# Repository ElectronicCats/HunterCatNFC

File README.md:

# Hunter Cat NFC

<p align=center>

<p align=center>

</p>

## How does the Hunter Cat NFC work?

The Hunter Cat NFC is a security tool for contactless (Near Field Communication) used in access control, identification, and bank cards. It is specially created to identify NFC readers and sniffing tools. With this tool, you can audit, read or emulate cards of different types.

## Understanding the Hunter Cat NFC and its LEDs 

The device has preloaded reader detection firmware that lets the user know when is near an NFC reader attempting to read his card.

### Reader detection 

To detect hidden readers seeking to read your cards without authorization for cloning.

1. Turn on Hunter Cat NFC
2. Wait for the LEDs to turn off
3. Red LED flashes every 1 second
4. Approach the reader, the Hunter Cat NFC LEDs should light up indicating if an NFC reader was detected
5. If it does not turn on and the LED stays on, it is not near an NFC reader

## How does it work? 

Hunter Cat NFC can be set to behave either as an NFC reader, a tag, or to establish a two-way connection with another NFC device.

NFC USB Dongle features a SAMD21 MCU which works in conjunction with the PN7150. The USB interface is provided by SAMD21 MCU, and the NFC functionality is ensured thanks to PN7150.

NFC is designed to be intuitive for users. The communication between two devices is established in the simplest way possible — by bringing them close to each other. NFC frontend can operate in three distinct modes:

### Card emulation mode — where Hunter Cat NFC behaves like a smart card or a tag

In this mode, Hunter Cat NFC emulates a NFC tag. It doesn’t initiate the communication, it only responds to a NFC reader. A typical application of the card emulation mode is how people use NFC in their smartphones to replace several cards, badges or tags at once (using the same phone for RFID access controls, contactless payments and so on). Card emulation mode, however, is not limited to smartphones but can be used for any portable device.

### Read/Write — where Hunter Cat NFC behaves as an NFC Reader/Writer

Here, Hunter Cat NFC communicates with a passive tag, NFC smart card, or an NFC device operating in card emulation mode. It can read or write to a tag (although reading is a more common use-case because tags will often be write protected). In this mode, the Hunter Cat NFC generates the RF field, while a tag or card only modulates it.

### Peer-to-peer — for more complex interactions

Peer-to-peer mode establishes a two-way communication channel between a pair of NFC-enabled devices. When a user brings two devices close to each other, the two NFC chips establish a P2P connection and exchange data.

## Characteristics:
* Procesador Cortex M0+
* USB C 2.0
* NFC Reader, Card and NFC Forum
* Arduino compatible
* CircuitPython compatible
* UF2 Bootloader
* 3 LEDs status
* Open Hardware
* Battery
* RF protocols supported
  * NFCIP-1, NFCIP-2 protocol 
  * ISO/IEC 14443A, ISO/IEC 14443B PICC, NFC Forum T4T modes via host interface
  * NFC Forum T3T via host interface
  * ISO/IEC 14443A, ISO/IEC 14443B PCD designed according to NFC Forum digital protocol T4T platform and ISO-DEP 
  * FeliCa PCD mode
  * MIFARE Classic PCD encryption mechanism (MIFARE Classic 1K/4K)
  * NFC Forum tag 1 to 5 (MIFARE Ultralight, Jewel, Open FeliCa tag, MIFAREDESFire
  * ISO/IEC 15693/ICODE VCD mode 
  * Includes NXP ISO/IEC14443-A and Innovatron ISO/IEC14443-B intellectual property licensing rights

## Disclaimer
>[!IMPORTANT]
>Hunter Cat NFC, is a wireless penetration testing tool intended solely for use in authorized security audits, where such usage is permitted by applicable laws and regulations. Before utilizing this tool, it is crucial to ensure compliance with all relevant legal requirements and obtain appropriate permissions from the relevant authorities.
>
>It is essential to note that the board does not provide any means or authorization to utilize credit cards or engage in any financial transactions that are not legally authorized. Electronic Cats holds no responsibility for any unauthorized use of the tool or any resulting damages.

## How to contribute 
 Contributions are welcome! 

Please read the document [**Contribution Manual**](https://github.com/ElectronicCats/electroniccats-cla/blob/main/electroniccats-contribution-manual.md)  which will show you how to contribute your changes to the project.

✨ Thanks to all our [contributors](https://github.com/ElectronicCats/HunterCatNFC/graphs/contributors)! ✨

See  [**_Electronic Cats CLA_**](https://github.com/ElectronicCats/electroniccats-cla/blob/main/electroniccats-cla.md) for more information.

See the [**community code of conduct**](https://github.com/ElectronicCats/electroniccats-cla/blob/main/electroniccats-community-code-of-conduct.md)   for a vision of the community we want to build and what we expect from it.

## Donation

Electronic Cats invests time and resources in providing this open-source design. Please support Electronic Cats and open-source hardware by purchasing products from Electronic Cats!

Designed by Electronic Cats.

Firmware released under an GNU AGPL v3.0 license. See the LICENSE file for more information.

Hardware released under an CERN Open Hardware Licence v1.2. See the LICENSE_HARDWARE file for more information.

Electronic Cats is a registered trademark. Please do not use if you sell these PCBs.

November 2019

## License

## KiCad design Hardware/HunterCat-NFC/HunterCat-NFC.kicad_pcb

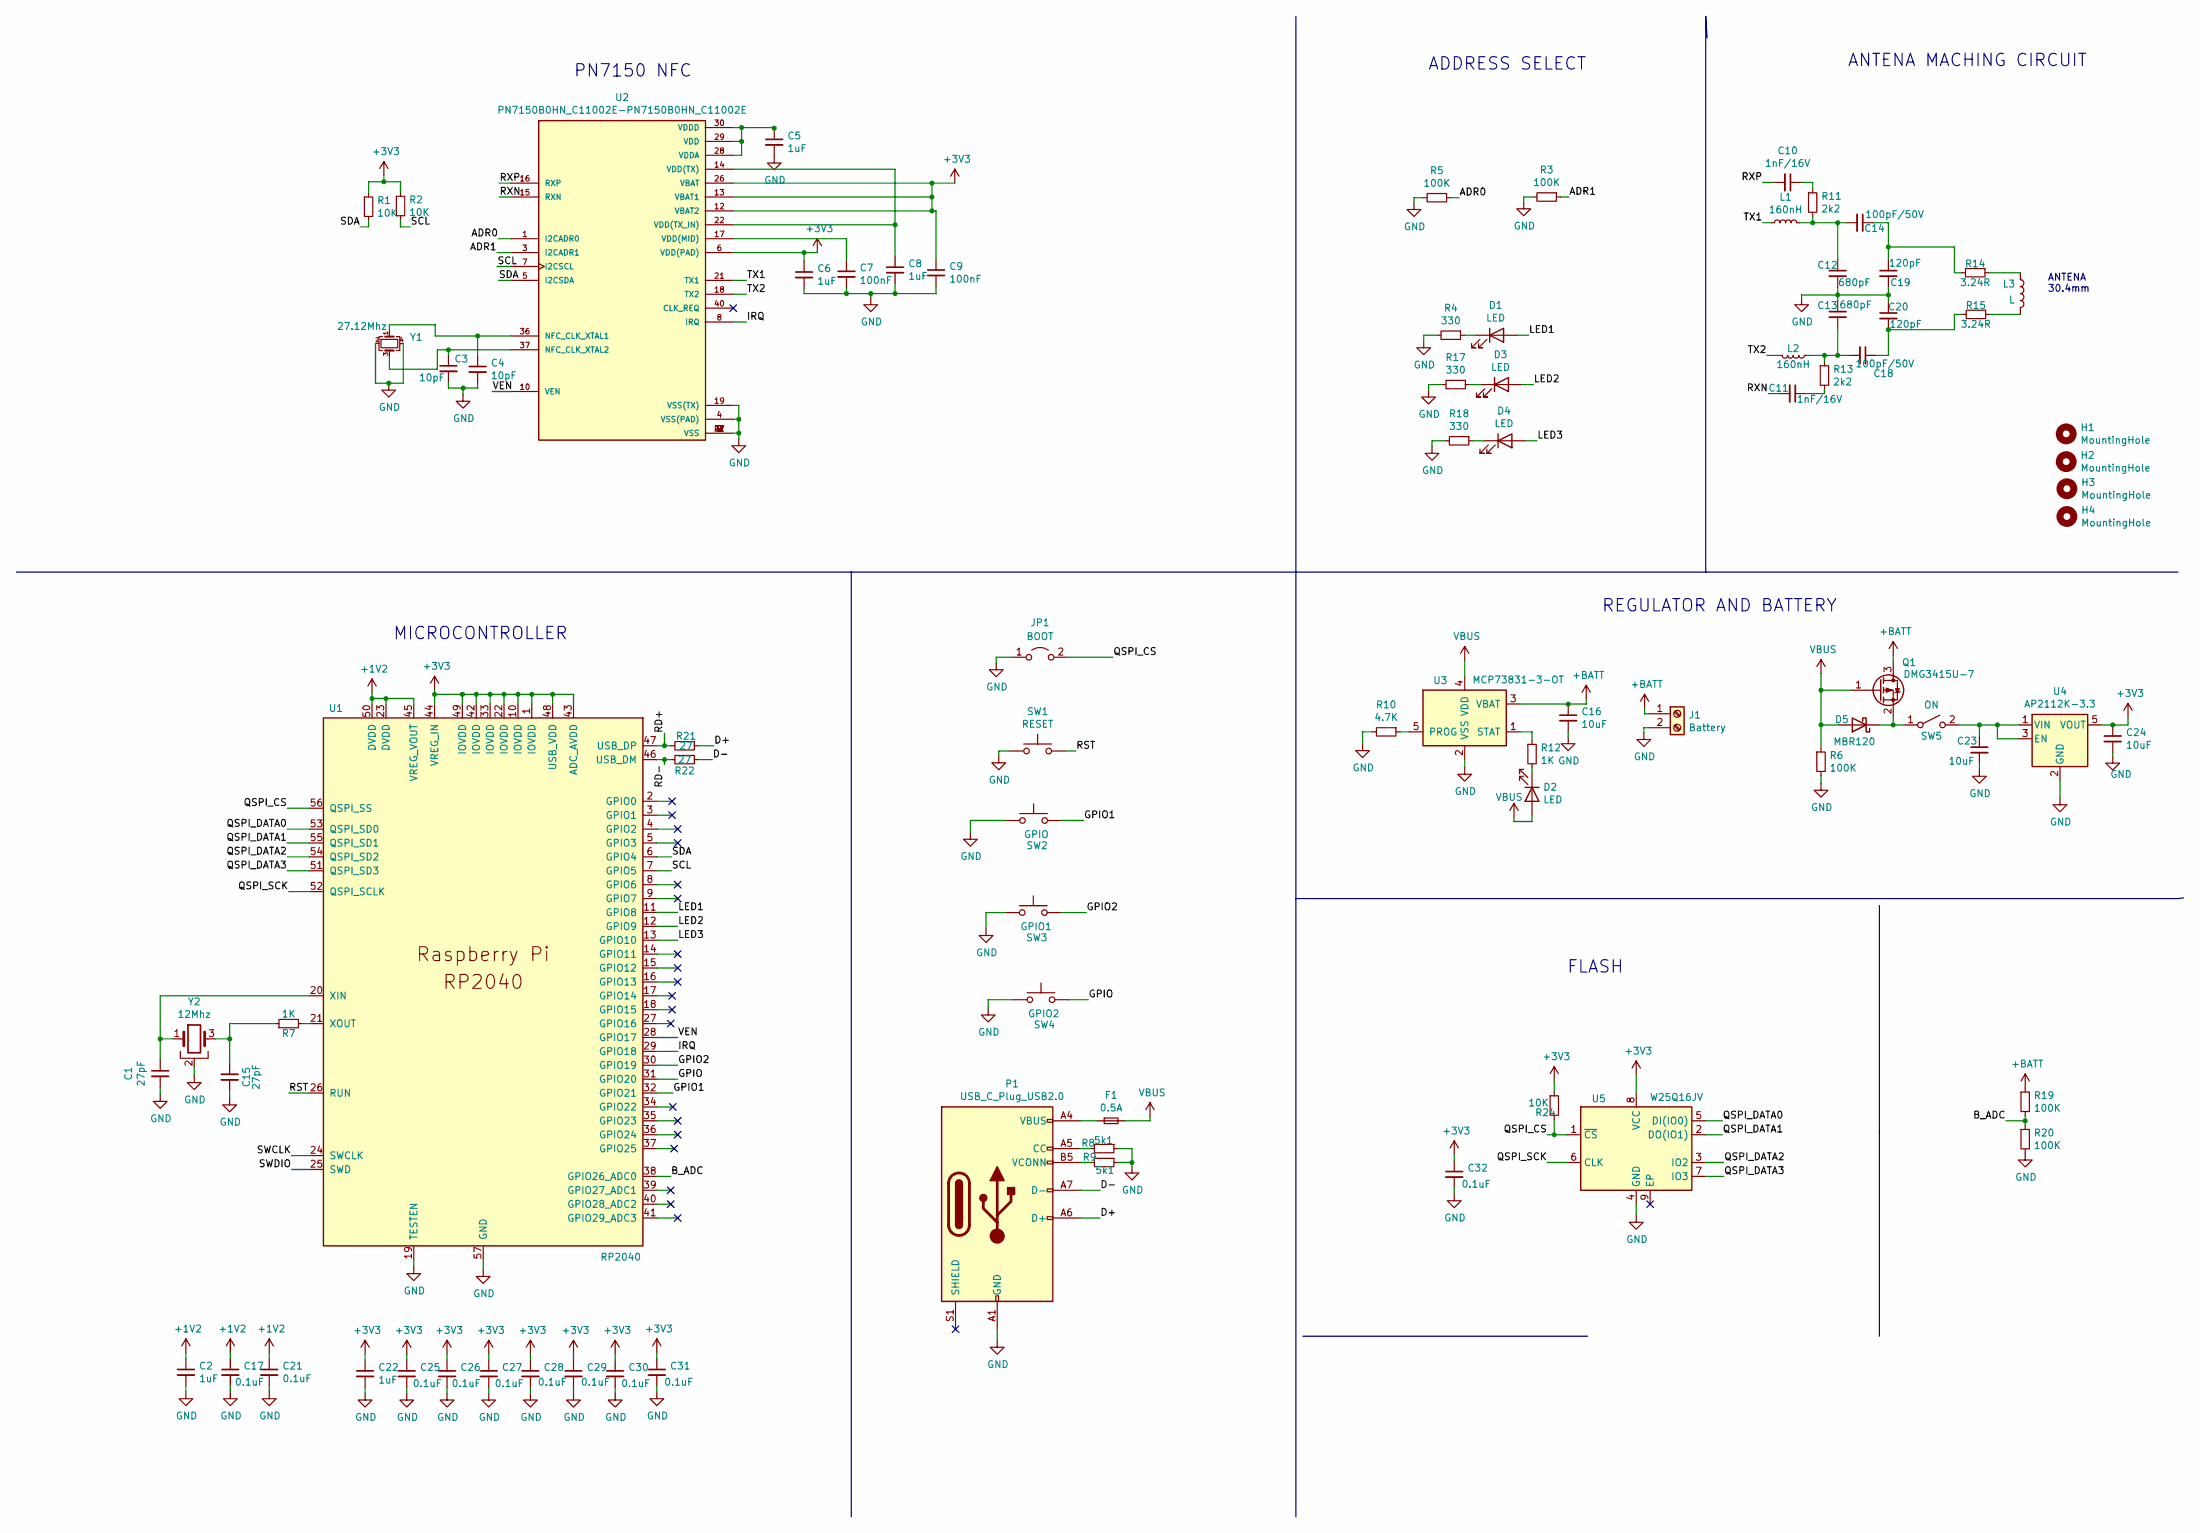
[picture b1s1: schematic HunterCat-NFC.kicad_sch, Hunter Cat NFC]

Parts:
C1, C15: 27pF; C_0603_1608Metric
C2, C22: 1uF; C_0603_1608Metric
C3, C4: 10pF; C_0603_1608Metric
C5, C6, C8: 1uF; C_0603_1608Metric; LCSC# C26413
C7, C9: 100nF; C_0603_1608Metric; LCSC# C387984
C10, C11: 1nF/16V; C_0603_1608Metric
C12, C13: 680pF; C_0603_1608Metric
C14, C18: 100pF/50V; C_0603_1608Metric
C16, C23, C24: 10uF; C_0603_1608Metric; LCSC# C326057
C17, C21, C25, C26, C27, C28, C29, C30, C31, C32: 0.1uF; C_0603_1608Metric
C19, C20: 120pF; C_0603_1608Metric
D1: LED; LED_0805_2012Metric_Pad1.15x1.40mm_HandSolder; LCSC# C130114
D2: LED; LED_0805_2012Metric_Pad1.15x1.40mm_HandSolder; LCSC# C205441
D3: LED; LED_0805_2012Metric_Pad1.15x1.40mm_HandSolder; LCSC# C205442
D4: LED; LED_0805_2012Metric_Pad1.15x1.40mm_HandSolder; LCSC# C84261
D5: MBR120; D_SOD-123F; LCSC# C723989
F1: 0.5A; Fuse_0603_1608Metric_Pad1.05x0.95mm_HandSolder
H1, H2, H3, H4: MountingHole; MountingHole_2.2mm_M2
J1: Battery; PinSocket_2x01_P2.54mm_Vertical_SMD
JP1: BOOT; SolderJumper-2_P1.3mm_Open_TrianglePad1.0x1.5mm
L1, L2: 160nH; L_0603_1608Metric_Pad1.05x0.95mm_HandSolder; LCSC# C434822
L3: L; NFC-antenna30.4x30.4mm
P1: USB_C_Plug_USB2.0; C393939; LCSC# C393939
Q1: DMG3415U-7; SOT-23; LCSC# C96616
R1, R2: 10K; R_0603_1608Metric; LCSC# C15401
R3, R5, R6, R19, R20: 100K; R_0603_1608Metric; LCSC# C15458
R4, R17, R18: 330; R_0603_1608Metric; LCSC# C517454
R7: 1K; R_0603_1608Metric
R8, R9: 5k1; R_0603_1608Metric; LCSC# C131715
R10: 4.7K; R_0603_1608Metric; LCSC# C116693
R11, R13: 2k2; R_0603_1608Metric; LCSC# C217937
R12: 1K; R_0603_1608Metric; LCSC# C517454
R14, R15: 3.24R; R_0603_1608Metric
R21, R22: 27; R_0603_1608Metric
R24: 10K; R_0603_1608Metric
SW1: RESET; KSC941JLFS; LCSC# C221771
SW2: GPIO; KSC941JLFS; LCSC# C221771
SW3: GPIO1; KSC941JLFS; LCSC# C221771
SW4: GPIO2; KSC941JLFS; LCSC# C221771
SW5: ON; Micro_interruptor_SPDT
U1: RP2040; RP2040-QFN-56
U2: PN7150B0HN_C11002E-PN7150B0HN_C11002E; QFN-40-1EP_6x6mm_P0.5mm_EP4.6x4.6mm
U3: MCP73831-3-OT; SOT-23-5
U4: AP2112K-3.3; SOT-23-5
U5: W25Q16JV; W25Q16JVUUIQ
Y1: 27.12Mhz; Crystal_SMD_2016-4Pin_2.0x1.6mm
Y2: 12Mhz; Crystal_SMD_2520-4Pin_2.5x2.0mm; LCSC# C709001

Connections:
+1V2: C2.1, C17.1, C21.1, U1.23 (DVDD), U1.45 (VREG_VOUT), U1.50 (DVDD)
+3V3: C6.1, C9.1, C22.1, C24.1, C25.1, C26.1, C27.1, C28.1, C29.1, C30.1, C31.1, C32.1, R1.1, R2.1, R24.1, U1.1 (IOVDD), U1.10 (IOVDD), U1.22 (IOVDD), U1.33 (IOVDD), U1.42 (IOVDD), U1.43 (ADC_AVDD), U1.44 (VREG_IN), U1.48 (USB_VDD), U1.49 (IOVDD), U2.6 (VDD(PAD)), U2.12 (VBAT2), U2.13 (VBAT1), U2.26 (VBAT), U4.5 (VOUT), U5.8 (VCC)
+BATT: C16.1, J1.1, Q1.3 (D), R19.1, U3.3 (VBAT)
/ADR0: R5.1, U2.1 (I2CADR0)
/ADR1: R3.1, U2.3 (I2CADR1)
/B_ADC: R19.2, R20.1, U1.38 (GPIO26_ADC0)
/D+: P1.A6 (D+), R21.1
/D-: P1.A7 (D-), R22.1
/GPIO: SW4.2, U1.31 (GPIO20)
/GPIO1: SW2.2, U1.32 (GPIO21)
/GPIO2: SW3.2, U1.30 (GPIO19)
/IRQ: U1.29 (GPIO18), U2.8 (IRQ)
/LED1: D1.2 (A), U1.11 (GPIO8)
/LED2: D3.2 (A), U1.12 (GPIO9)
/LED3: D4.2 (A), U1.13 (GPIO10)
/QSPI_CS: JP1.2 (B), R24.2, U1.56 (QSPI_SS), U5.1 (~CS)
/QSPI_DATA0: U1.53 (QSPI_SD0), U5.5 (DI(IO0))
/QSPI_DATA1: U1.55 (QSPI_SD1), U5.2 (DO(IO1))
/QSPI_DATA2: U1.54 (QSPI_SD2), U5.3 (IO2)
/QSPI_DATA3: U1.51 (QSPI_SD3), U5.7 (IO3)
/QSPI_SCK: U1.52 (QSPI_SCLK), U5.6 (CLK)
/RD+: R21.2, U1.47 (USB_DP)
/RD-: R22.2, U1.46 (USB_DM)
/RST: SW1.2, U1.26 (RUN)
/RXN: C11.2, U2.15 (RXN)
/RXP: C10.2, U2.16 (RXP)
/SCL: R2.2, U1.7 (GPIO5), U2.7 (I2CSCL)
/SDA: R1.2, U1.6 (GPIO4), U2.5 (I2CSDA)
/SWCLK: U1.24 (SWCLK)
/SWDIO: U1.25 (SWD)
/TX1: L1.1, U2.21 (TX1)
/TX2: L2.2, U2.18 (TX2)
/VEN: U1.28 (GPIO17), U2.10 (VEN)
GND: C1.2, C2.2, C3.2, C4.2, C5.2, C6.2, C7.2, C8.2, C9.2, C12.2, C13.1, C15.2, C16.2, C17.2, C19.2, C20.1, C21.2, C22.2, C23.2, C24.2, C25.2, C26.2, C27.2, C28.2, C29.2, C30.2, C31.2, C32.2, J1.2, JP1.1 (A), P1.A1 (GND), P1.A12 (GND), P1.B1 (GND), P1.B12 (GND), R3.2, R4.2, R5.2, R6.2, R8.1, R9.1, R10.2, R17.2, R18.2, R20.2, SW1.1, SW2.1, SW3.1, SW4.1, U1.19 (TESTEN), U1.57 (GND), U2.2 (VSS), U2.4 (VSS(PAD)), U2.9 (VSS), U2.19 (VSS(TX)), U2.27 (VSS), U2.41 (VSS), U3.2 (VSS), U4.2 (GND), U5.4 (GND), Y1.2, Y1.4, Y2.2
unnamed: C1.1, U1.20 (XIN), Y2.1
unnamed: C3.1, U2.37 (NFC_CLK_XTAL2), Y1.3
unnamed: C4.1, U2.36 (NFC_CLK_XTAL1), Y1.1
unnamed: C5.1, U2.28 (VDDA), U2.29 (VDD), U2.30 (VDDD)
unnamed: C7.1, U2.17 (VDD(MID))
unnamed: C8.1, U2.14 (VDD(TX)), U2.22 (VDD(TX_IN))
unnamed: C10.1, R11.1
unnamed: C11.1, R13.2
unnamed: C12.1, C14.2, L1.2, R11.2
unnamed: C13.2, C18.2, L2.1, R13.1
unnamed: C14.1, C19.1, R14.2
unnamed: C15.1, R7.1, Y2.3
unnamed: C18.1, C20.2, R15.2
unnamed: C23.1, SW5.2 (B), U4.1 (VIN), U4.3 (EN)
unnamed: D1.1 (K), R4.1
unnamed: D2.1 (K), R12.2
unnamed: D3.1 (K), R17.1
unnamed: D4.1 (K), R18.1
unnamed: D5.1 (K), Q1.2 (S), SW5.1 (A)
unnamed: F1.1, P1.A4 (VBUS), P1.A9 (VBUS), P1.B4 (VBUS), P1.B9 (VBUS)
unnamed: L3.1, R14.1
unnamed: L3.2, R15.1
unnamed: P1.A5 (CC), R8.2
unnamed: P1.B5 (VCONN), R9.2
unnamed: R7.2, U1.21 (XOUT)
unnamed: R10.1, U3.5 (PROG)
unnamed: R12.1, U3.1 (STAT)
VBUS: D2.2 (A), D5.2 (A), F1.2, Q1.1 (G), R6.1, U3.4 (VDD)

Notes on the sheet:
ADDRESS SELECT
PN7150 NFC
ANTENA MACHING CIRCUIT
REGULATOR AND BATTERY
MICROCONTROLLER
FLASH
ANTENA 30.4mm

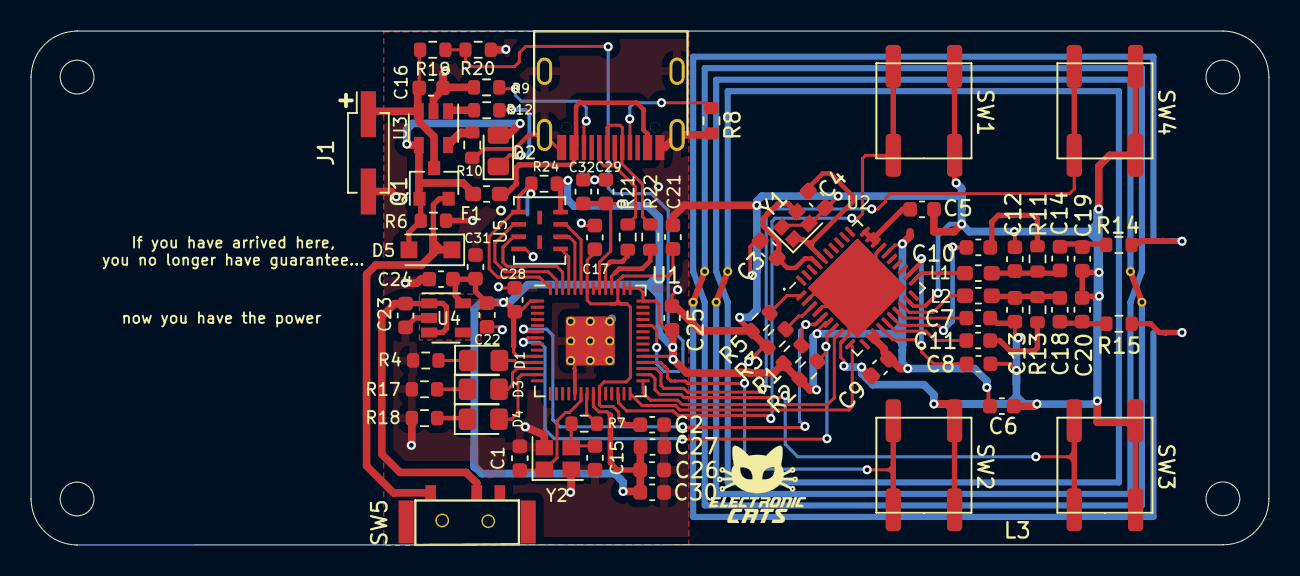
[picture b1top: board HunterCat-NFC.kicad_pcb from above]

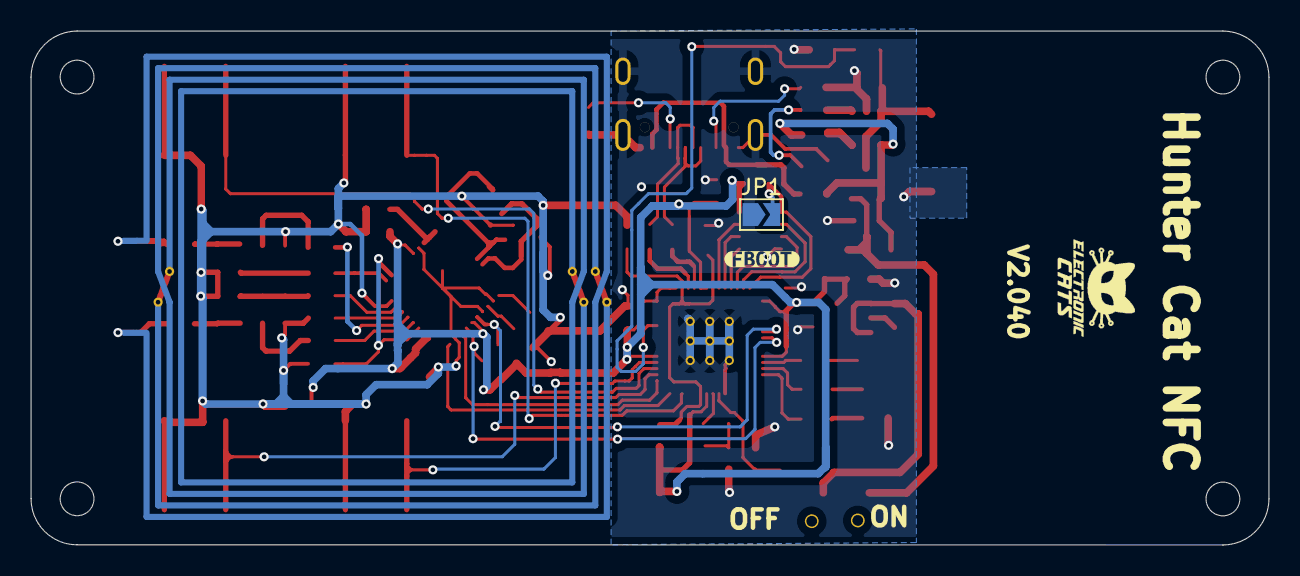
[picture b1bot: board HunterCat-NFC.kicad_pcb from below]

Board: 2 copper layers, 80.7 x 33.5 mm, 84 parts (3 on the bottom side), 60 nets.

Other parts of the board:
kibuzzard-62BD092C: G***; kibuzzard-62BD092C

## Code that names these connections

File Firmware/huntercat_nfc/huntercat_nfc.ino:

/**
   Example to detect NFC readers, read a Mifare Card, read a Visa card
   and emulate a Visa MSD card.

   Authors:
          Salvador Mendoza - @Netxing - salmg.net
          For Electronic Cats - electroniccats.com

   March 2021

   This code is beerware; if you see me (or any other collaborator
   member) at the local, and you've found our code helpful,
   please buy us a round!
   Distributed as-is; no warranty is given.

   ---
   
   This code will detect NFC card readers.

   When it starts, the three LEDs will be on, and then will turn off after a second.
   Then a constant LED 1 will start flashing meaning that is scanning for NFC readers.
   When a NFC reader is detected, LED 2 and 3 will be on for a second.
   
*/

#include "Electroniccats_PN7150.h"

#define PN7150_IRQ   (15)
#define PN7150_VEN   (14)
#define PN7150_ADDR  (0x28)

Electroniccats_PN7150 nfc(PN7150_IRQ, PN7150_VEN, PN7150_ADDR);  // creates a global NFC device interface object, attached to pins 7 (IRQ) and 8 (VEN) and using the default I2C address 0x28
RfIntf_t RfInterface;                                            //Intarface to save data for multiple tags

unsigned char STATUSOK[] = {0x90, 0x00}, Cmd[256], CmdSize;

uint8_t mode = 2;  // modes: 1 = Reader/ Writer, 2 = Emulation

void RGB(int R, int G, int B)
{
  int g = map(G, 0, 255, 0, 1023);
  
  analogWrite(PIN_LED,R);
  analogWrite(PIN_LED2,B);
  analogWrite(PIN_LED3,g);
}

void blink(int pin, int msdelay, int times) {
  for (int i = 0; i < times; i++) {
    digitalWrite(pin, HIGH);
    delay(msdelay);
    digitalWrite(pin, LOW);
    delay(msdelay);
  }
}

void setup() {
  Serial.begin(9600);
  //while (!Serial);
  Serial.println("Detecting NFC readers with PN7150");
  
  pinMode(LED_BUILTIN, OUTPUT); //RED
  pinMode(PIN_LED2, OUTPUT);
  pinMode(PIN_LED3, OUTPUT);

  digitalWrite(LED_BUILTIN, LOW);
  digitalWrite(PIN_LED2, LOW);
  digitalWrite(PIN_LED3, LOW);

  Serial.println("Initializing...");
  if (nfc.connectNCI()) { //Wake up the board
    Serial.println("Error while setting up the mode, check connections!");
    while (1){
      blink(LED_BUILTIN, 200, 3);
    }
  }

  if (nfc.ConfigureSettings()) {
    Serial.println("The Configure Settings failed!");
    while (1){
      blink(LED_BUILTIN, 200, 5);
    }
  }

  if (nfc.ConfigMode(mode)) { //Set up the configuration mode
    Serial.println("The Configure Mode failed!!");
    while (1){
      blink(LED_BUILTIN, 200, 10);
    }
  }
  nfc.StartDiscovery(mode); //NCI Discovery mode
  blink(LED_BUILTIN, 200, 2);
  blink(PIN_LED2, 200, 2);
  blink(PIN_LED3, 200, 2);
  Serial.println("HunterCat NFC v1.3");
  Serial.println("Looking for card readers...");
}

// to detect NFC card readers
void loop() {
  
  if (nfc.CardModeReceive(Cmd, &CmdSize) == 0) { //Data in buffer?
    if ((CmdSize >= 2) && (Cmd[0] == 0x00)) { //Expect at least two bytes
      switch (Cmd[1]) {
        case 0xA4: //If tries to select a file, meaning that it is a reader
          Serial.println("Card reader detected!");
          digitalWrite(PIN_LED2, HIGH);
          digitalWrite(PIN_LED3, HIGH);
          delay(1000);
          digitalWrite(PIN_LED2, LOW);
          digitalWrite(PIN_LED3, LOW);
          break;

        default:
          break;
      }
      nfc.CardModeSend(STATUSOK, sizeof(STATUSOK));
    }
  }
  
  int analog = analogRead(A0);
  int voltagepercent = map(analog, 0, 645, 0, 100 );
  
  //Low Battery < 30%
  if(voltagepercent < 30){
    RGB(234, 200, 203); //Pink
    delay(100);
    RGB(0, 0, 0);
    delay(100);
  }
  
  blink(LED_BUILTIN, 10, 1);
}

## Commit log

2020-02-11 PN7150 basic schematic
2020-02-11 add samd21e
2020-02-12 alpha version
2020-02-12 add addres select I2C
2020-02-12 update components
2020-03-09 add SPI flash and ADC Battery
2020-03-10 add SPI pins
2020-03-25 add antennas footprints
2020-03-26 Update libraries, add antenna 30x30mm
2020-03-26 update sheet
2020-03-27 new size for hunter cat family
2020-03-29 fix GND crystal
2020-04-03 Routeo
2020-04-03 add connector test breakout
2020-04-08 update pcb
2020-04-08 add footprint crystal and battery connector
2020-04-08 fix routeo
2020-04-09 add c25
2020-04-09 add logos
2020-04-10 value c25
2020-04-10 Fix routes and component placement, ground plane not on antenna
2020-04-10 fix label
2020-04-10 Update SPI Flash and Gerbers settings
2020-04-10 Add beta testing logo
2020-04-16 manf#
2020-04-21 change manf#
2020-07-27 Reduction
2020-07-27 Change sch
2020-07-29 Fix Batt source
2020-07-29 labels size
2020-08-02 Last change
2020-08-05 Case
2020-08-06 select case
2020-08-07 Last revision
2020-08-07 Add screws
2020-08-07 New Case
2020-08-17 modify Rf frontend
2020-08-20 Add button
2020-08-25 new size
2020-08-28 Change ant
2020-08-28 Change Position
2020-08-31 new labels
2020-09-01 Mounting Hole
2020-09-01 Mounting_Hole
2020-09-01 modify coil holes
2020-09-29 Update labels VEN and IRQ
2020-10-06 fix mosfet and battery voltage
2020-10-06 update v1.1 2 layes
2020-10-06 fiz silk and layout
2020-10-06 update traces
2020-10-06 minor silkscreen changes
2020-10-19 add logos and mounitng holes again
2020-10-19 Accommodated screw holes
2020-10-20 add switch on off
2020-10-20 Added a new step
2020-10-22 Moved the battery footprint
2020-10-27 Moved footprints
2020-10-27 Case holes placement
2020-11-05 update case
2020-11-05 Update setting pcb
2020-11-10 update BOM
2020-11-12 update v1.2 footprint
2020-11-12 New_Case
2020-11-13 update graphic
2020-11-13 Fixed Case
2020-11-13 Fixed Led window
2020-11-26 fix B.Silks
2020-12-01 Add_Labels_and_Footprint
2020-12-01 fix label on/off
2020-12-01 Move_connector
2020-12-15 The PCB became more symmetric
2020-12-15 moved some labels
2020-12-15 Symmetric design (case and acrylic)
2020-12-30 rename folder hardware
2020-12-30 move file
2021-01-12 Add firmware
2021-01-12 Added LED and Buttons for define
2021-01-21 update flash memmory
2021-01-25 define DEBUG
2021-02-05 Added .dxf archive
2021-03-09 Update card readers
2021-03-21 Update pre-order REDME
2021-03-24 add leds error
2021-03-24 Add RGB leds control and low Battery
2021-03-24 update version
2021-03-24 update F.Cu case
2021-03-27 init AllOne example
2021-03-27 remove duplicate function
2021-03-27 Add Emulate Visa MSD
2021-03-27 rename detect readers example
2021-03-27 update info
2021-03-27 fix define KEY_MFC
2021-03-28 remove variable exc
2021-03-28 change resetMode void
2021-03-28 typo detecCardFlag
2021-03-29 Create LICENSE
2021-03-29 Rename LICENSE_HARDWARE.md to LICENSE_HARDWARE
2021-03-29 Validate external flash
2021-03-30 validate flash
2021-03-30 add RGB control
2021-03-30 add battery notification
2021-03-30 format code
2021-04-01 add bin for testing with bootloader included
2021-04-08 fixLedLowBattery
2021-04-12 addP2PExample
2021-04-12 chngScriptLabels
2021-04-15 add LED error configuration and init
2021-04-22 fixLEDsBlink
2021-05-02 Add support example amiibo
    Read/Write Amiibo based in work by https://games.kel.mn/en/create-amiibo-clones-with-arduino-and-pn532-nfc-module/
2022-02-22 Change_Crystal
2022-05-12 Update gitgnore backups
2022-06-22 Replace ATSAND21E18A with RP2040
2022-06-23 Replace RP2040 pins labels
2022-06-23 Assigned footprints
2022-06-24 Replace RP2040 crystal footprint
2022-06-28 Starting the change of PCB design
2022-06-28 change button for jumper force boot
2022-06-30 update labels v2.040
    version for RP2040
2022-07-16 add notconnect
2022-07-29 add allOne for version RP2040
2022-07-29 change resistor charger
2022-08-06 Example for RP2040 picoCore
2022-08-06 Update examples for RP2040
2022-08-23 Update README.md
    Wiki added and some corrections
2022-09-29 Create stale config
2022-09-29 Issue template added
2022-10-10 add ifdef DEBUG
2022-11-10 clone UID
2022-11-14 clone UID ok
2022-11-14 Update with UID Clone
2022-11-23 Changed charge resistance to 4.7K and updated BOM
2023-01-26 Fixed Typos
2023-03-08 Changed Button
2023-06-14 Add Disclaimer
2023-09-16 add button donation
2023-12-22 change store button
2024-04-08 feat(docs):Update README.md
    Add CLA
